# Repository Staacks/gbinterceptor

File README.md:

# GB Interceptor
Capture or stream Game Boy gameplay footage via USB without modifying the Game Boy.

This open source and open hardware Game Boy adapter uses an rp2040 to capture the communication on the cartridge bus. This data is fed into an emulator, rendered and then offered as a USB video class device.

Details about the concept can be found at https://there.oughta.be/a/game-boy-capture-cartridge and an overview is given in the following video:

If you have pull-requests, bug reports or want to contribute new case designs, please do not hesitate to open an issue. For generic discussions, "show and tell" and if you are looking for support for something that is not a problem in the code here, I would recommend .

# Warnings

Please make sure to understand what this device does and what its limitations are. Most importantly, there is a little lag which will make it unsuitable for playing on a bis screen. It might be ok for slow games, but its focus is on recording and streaming.

Also check out the compatibility tables for host software (for example OBS) and particular games. In principle this is a USB video class device and does not require drivers, but not all software supports the unsusual video format of the Interceptor. Similarly, games should usually work, but sometimes there are some details that the Interceptor does not yet support properly and some rare things that cannot work based on the principle of this device.

* [Game Boy compatibility](https://github.com/Staacks/gbinterceptor/wiki/Game-Boy-compatibility)
* [Host software compatibility](https://github.com/Staacks/gbinterceptor/wiki/Host-software-compatibility)
* [Game compatibility](https://github.com/Staacks/gbinterceptor/wiki/Game-compatibility)

# Building the Interceptor

There is an [order and build video](https://youtu.be/Lg92tVkEE98) to guide you through the build process which I highly recommend, especially if you are not used to ordering PCBs. A [written guide can be found in this repository's wiki](https://github.com/Staacks/gbinterceptor/wiki/Build-guide).

# Usage

Simply plug the Interceptor into your Game Boy and the Game into the Interceptor. Connect the Interceptor to your computer before turning on the Game Boy. It should show up as a webcam in any software that supports USB Video devices (for example OBS Studio). Note that some software is not entirely happy with the exotic format, but it should work in most cases (see [Host software compatibility](https://github.com/Staacks/gbinterceptor/wiki/Host-software-compatibility)).

Then just turn on the Game Boy and play.

Note that you do not need to open the video stream first. The only important step is that the Interceptor is powered via USB before the Game Boy is turned on.

## Buttons

The [Mode] button (next to the LEDs) allows to switch between grayscale/green colors and toggle frame blending. Each press switches colors and frame blending is toggled each time it returns to grayscale.

The [Flash] button (near the center, usually inside the case) is only used to flash a new firmware version. Simply hold it while plugging in the USB cable. The Interceptor should appear as a storage device (like a USB stick) and you can simply drag the new firmware file (a uf2 file) into it.

## LEDs

The red LED indicates that the Interceptor is powered.

The blue LED stays on as long as the Interceptor is in sync with the game. (It may shortly turn off for a fraction of a second when the Game Boy turns the display off, i.e. when loading a level.)

# Support

While I do not give any guarantees I (and probably others too) am happy to help if I have the time.

If you are having difficulties to order, build or use your Interceptor, please do not contact me directly but use [r/thereoughtabe on reddit](https://www.reddit.com/r/thereoughtabe/) as this allows others to help and the answer might help others, too.

If you found a bug and in particular if you find glitches in a game, please check the [compatibility lists](https://github.com/Staacks/gbinterceptor/wiki) in the Wiki first to see if it is a known problem and open an issue here on Github otherwise.

# Building the firmware

Most users should just install the latest release uf2 as described in the [Build guide](https://github.com/Staacks/gbinterceptor/wiki/Build-guide), but if you want to build it yourself, you will need the [Raspberry Pi Pico SDK](https://github.com/raspberrypi/pico-sdk). Don't forget to set PICO_SDK_PATH accordingly.

Make sure to check out the submodules too and specifically make sure that the [TinyUSB](https://github.com/hathach/tinyusb) submodule is at least on version 0.14.0 as the Pico SDK currently references an older version. (Also see [#3](https://github.com/Staacks/gbinterceptor/issues/3))

# License
The code is released under the GNU General Public Licence 3 and the design files (PCB layout and 3d printed case) are released under the Creative Commons licence CC-BY 4.0.

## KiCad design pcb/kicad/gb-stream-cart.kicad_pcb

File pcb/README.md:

# GB Interceptor PCB

These are the design files for the PCB of the GB Interceptor. See the [build guide](https://github.com/Staacks/gbinterceptor/wiki/Build-guide) for details.

# License

The design files are licensed under the Creative Commons Attribution License (CC-BY 4.0).

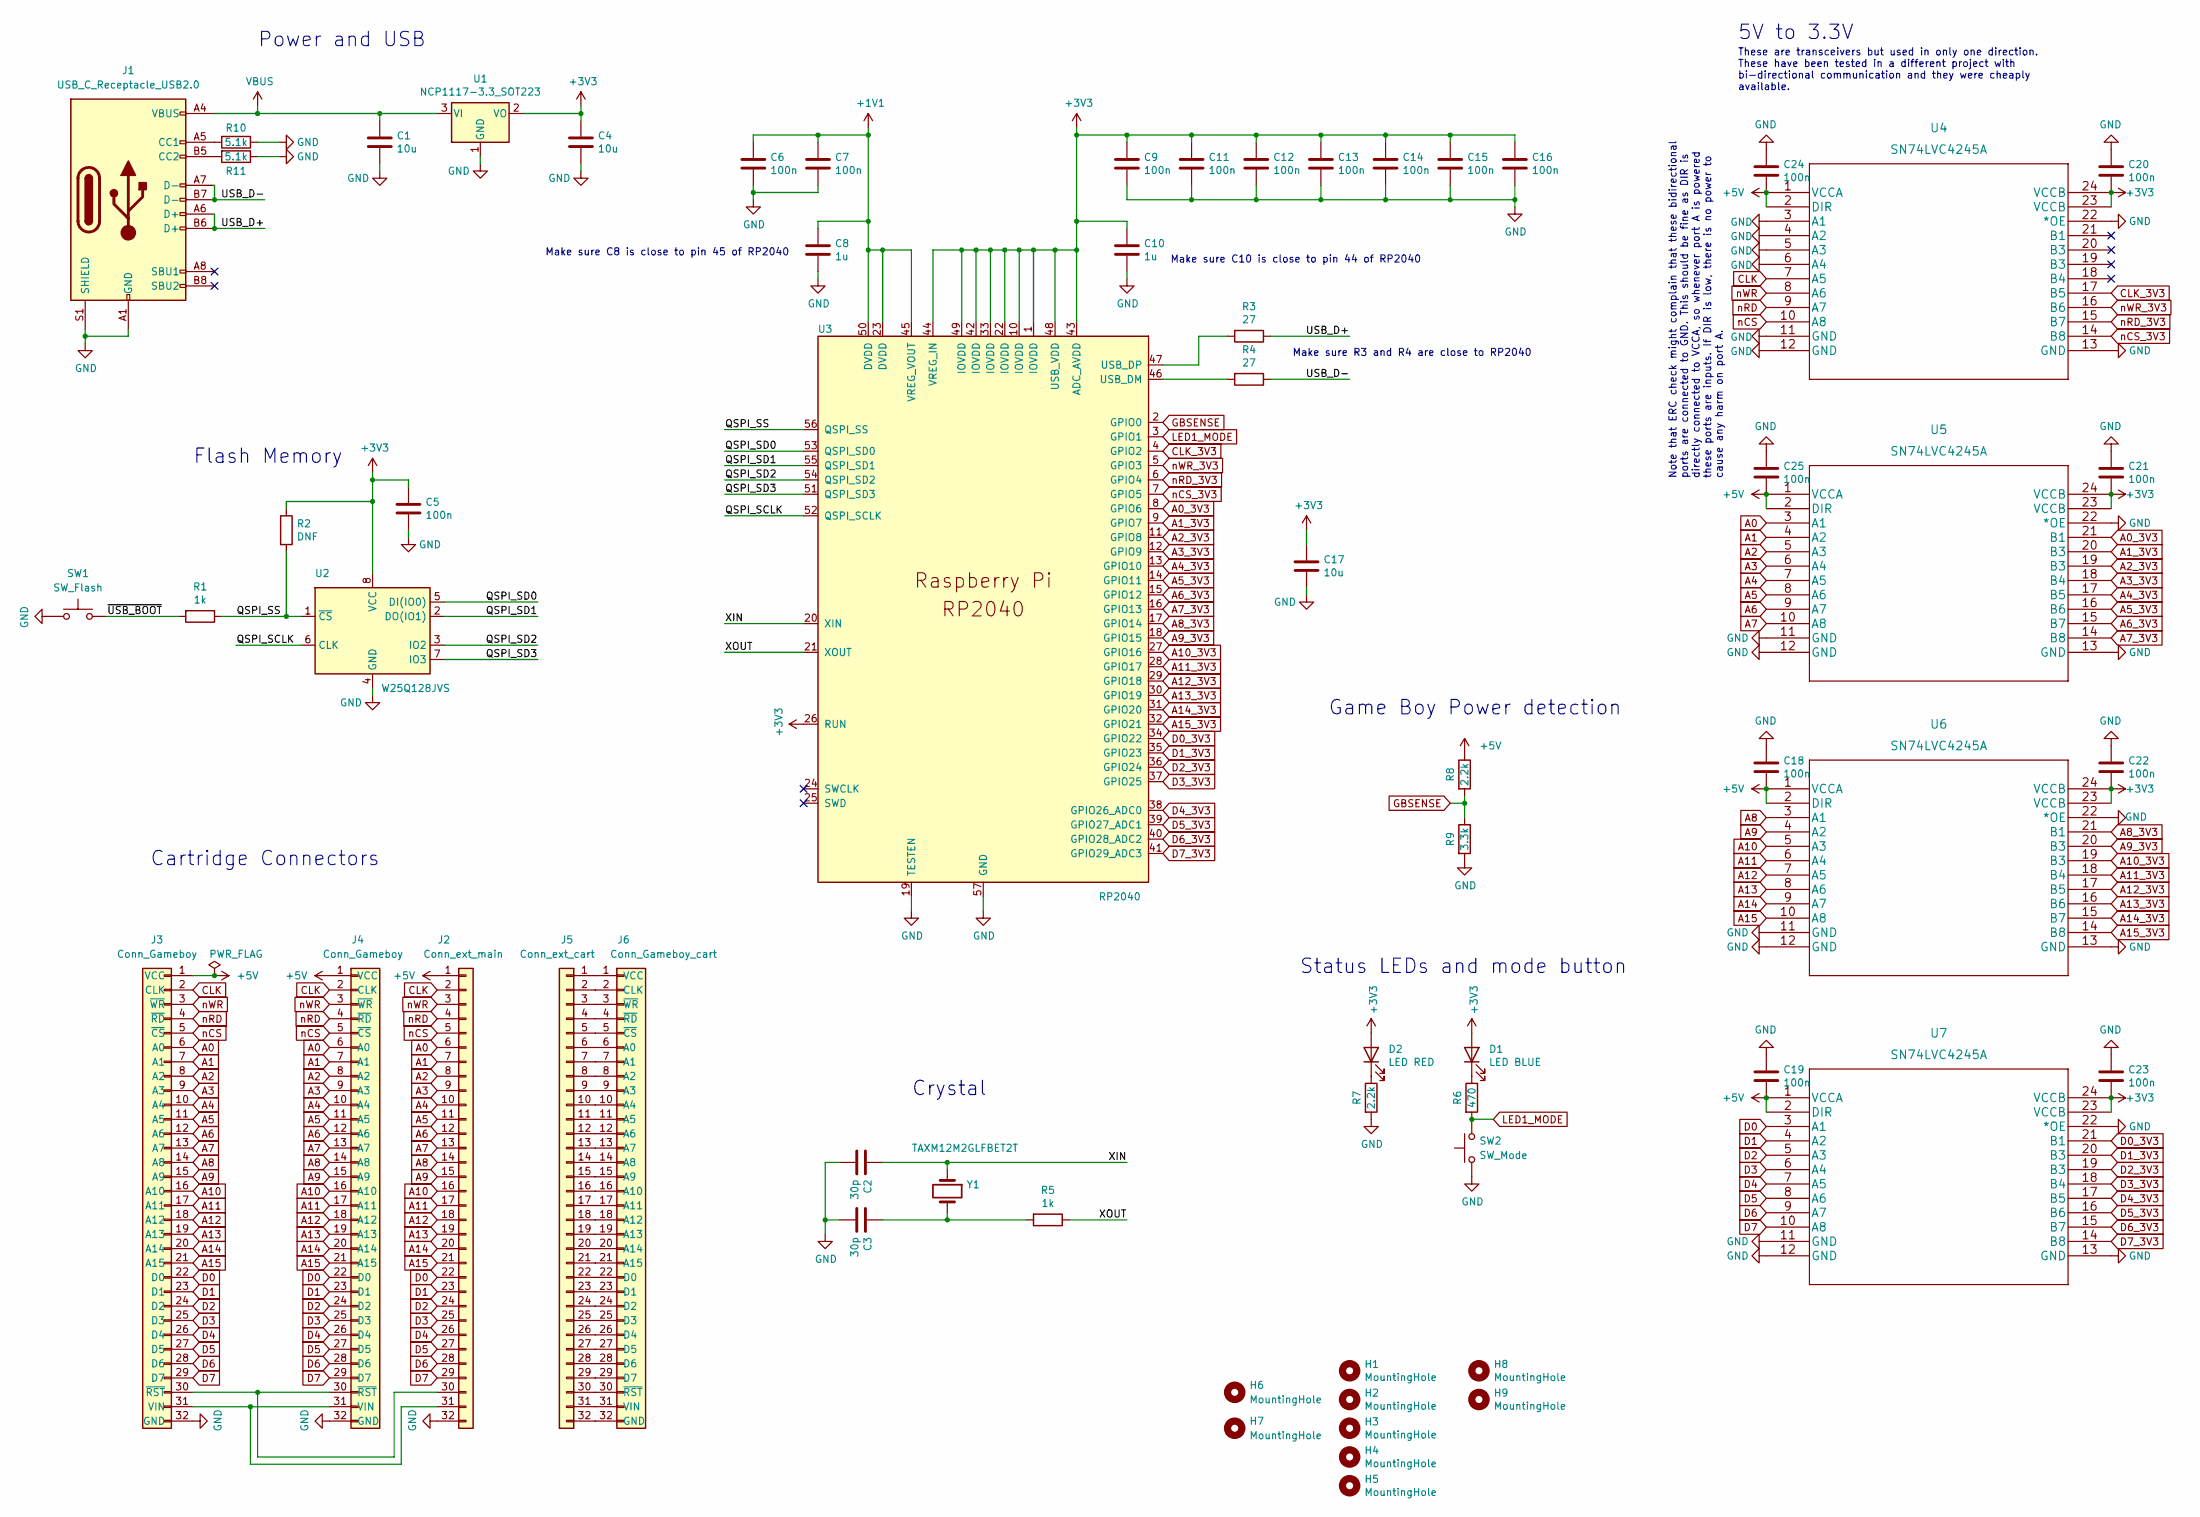
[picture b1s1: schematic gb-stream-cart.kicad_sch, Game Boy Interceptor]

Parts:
C1, C4, C17: 10u; C_0805_2012Metric; LCSC C440198
C2, C3: 30p; C_0402_1005Metric; LCSC C1570
C5, C6, C7, C9, C11, C12, C13, C14, C15, C16, C18, C19, C20, C21, C22, C23, C24, C25: 100n; C_0402_1005Metric; LCSC C1525
C8, C10: 1u; C_0402_1005Metric; LCSC C52923
D1: LED BLUE; LED_1206_3216Metric; LCSC C130717
D2: LED RED; LED_1206_3216Metric; LCSC C84270
H1, H2, H3, H4, H5, H8, H9: MountingHole; MountingHole_2.7mm_M2.5
H6: MountingHole; MountingHole_8.4mm_M8
H7: MountingHole; MountingHole_2.2mm_M2
J1: USB_C_Receptacle_USB2.0; USB_C_Receptacle_HRO_TYPE-C-31-M-12; LCSC C165948
J2: Conn_ext_main; PinHeader_2x16_P2.54mm_Horizontal
J3: Conn_Gameboy; cartridge_PCBedge
J4: Conn_Gameboy; cartridge-slot
J5: Conn_ext_cart; PinHeader_2x16_P2.54mm_Horizontal
J6: Conn_Gameboy_cart; cartridge-slot
R1, R5: 1k; R_0402_1005Metric; LCSC C11702
R2: DNF; R_0402_1005Metric
R3, R4: 27; R_0402_1005Metric; LCSC C25100
R6: 470; R_0402_1005Metric; LCSC C25117
R7, R8: 2.2k; R_0402_1005Metric; LCSC C25879
R9: 3.3k; R_0402_1005Metric; LCSC C25890
R10, R11: 5.1k; R_0402_1005Metric; LCSC C25905
SW1: SW_Flash; SW_Push_1P1T-SH_NO_CK_KMR2xxG; LCSC C72443
SW2: SW_Mode; SW_Push_1P1T-SH_NO_CK_KMR2xxG; LCSC C72443
U1: NCP1117-3.3_SOT223; SOT-223-3_TabPin2; LCSC C146799
U2: W25Q128JVS; SOIC-8_5.23x5.23mm_P1.27mm; LCSC C97521
U3: RP2040; RP2040-QFN-56; LCSC C2040
U4, U5, U6, U7: SN74LVC4245A; SN74LVC4245APWR; LCSC C7859
Y1: TAXM12M2GLFBET2T; Crystal_SMD_HC49-US; LCSC C111117

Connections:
+1V1: C6.1, C7.1, C8.1, U3.23 (DVDD), U3.45 (VREG_VOUT), U3.50 (DVDD)
+3V3: C4.1, C5.1, C9.1, C10.1, C11.1, C12.1, C13.1, C14.1, C15.1, C16.1, C17.1, C20.2, C21.2, C22.2, C23.2, D1.2 (A), D2.2 (A), R2.1, U1.2 (VO), U2.8 (VCC), U3.1 (IOVDD), U3.10 (IOVDD), U3.22 (IOVDD), U3.26 (RUN), U3.33 (IOVDD), U3.42 (IOVDD), U3.43 (ADC_AVDD), U3.44 (VREG_IN), U3.48 (USB_VDD), U3.49 (IOVDD), U4.23 (VCCB), U4.24 (VCCB), U5.23 (VCCB), U5.24 (VCCB), U6.23 (VCCB), U6.24 (VCCB), U7.23 (VCCB), U7.24 (VCCB)
+5V: C18.2, C19.2, C24.2, C25.2, J2.1, J3.1 (VCC), J4.1 (VCC), R8.1, U4.1 (VCCA), U4.2 (DIR), U5.1 (VCCA), U5.2 (DIR), U6.1 (VCCA), U6.2 (DIR), U7.1 (VCCA), U7.2 (DIR)
/QSPI_SCLK: U2.6 (CLK), U3.52 (QSPI_SCLK)
/QSPI_SD0: U2.5 (DI(IO0)), U3.53 (QSPI_SD0)
/QSPI_SD1: U2.2 (DO(IO1)), U3.55 (QSPI_SD1)
/QSPI_SD2: U2.3 (IO2), U3.54 (QSPI_SD2)
/QSPI_SD3: U2.7 (IO3), U3.51 (QSPI_SD3)
/QSPI_SS: R1.1, R2.2, U2.1 (~CS), U3.56 (QSPI_SS)
/USB_D+: J1.A6 (D+), J1.B6 (D+), R3.1
/USB_D-: J1.A7 (D-), J1.B7 (D-), R4.1
/XIN: C2.1, U3.20 (XIN), Y1.1
/XOUT: R5.1, U3.21 (XOUT)
/~USB_BOOT: R1.2, SW1.2
A0: J2.6, J3.6 (A0), J4.6 (A0), U5.3 (A1)
A0_3V3: U3.8 (GPIO6), U5.21 (B1)
A1: J2.7, J3.7 (A1), J4.7 (A1), U5.4 (A2)
A1_3V3: U3.9 (GPIO7), U5.20 (B3)
A2: J2.8, J3.8 (A2), J4.8 (A2), U5.5 (A3)
A2_3V3: U3.11 (GPIO8), U5.19 (B3)
A3: J2.9, J3.9 (A3), J4.9 (A3), U5.6 (A4)
A3_3V3: U3.12 (GPIO9), U5.18 (B4)
A4: J2.10, J3.10 (A4), J4.10 (A4), U5.7 (A5)
A4_3V3: U3.13 (GPIO10), U5.17 (B5)
A5: J2.11, J3.11 (A5), J4.11 (A5), U5.8 (A6)
A5_3V3: U3.14 (GPIO11), U5.16 (B6)
A6: J2.12, J3.12 (A6), J4.12 (A6), U5.9 (A7)
A6_3V3: U3.15 (GPIO12), U5.15 (B7)
A7: J2.13, J3.13 (A7), J4.13 (A7), U5.10 (A8)
A7_3V3: U3.16 (GPIO13), U5.14 (B8)
A8: J2.14, J3.14 (A8), J4.14 (A8), U6.3 (A1)
A8_3V3: U3.17 (GPIO14), U6.21 (B1)
A9: J2.15, J3.15 (A9), J4.15 (A9), U6.4 (A2)
A9_3V3: U3.18 (GPIO15), U6.20 (B3)
A10: J2.16, J3.16 (A10), J4.16 (A10), U6.5 (A3)
A10_3V3: U3.27 (GPIO16), U6.19 (B3)
A11: J2.17, J3.17 (A11), J4.17 (A11), U6.6 (A4)
A11_3V3: U3.28 (GPIO17), U6.18 (B4)
A12: J2.18, J3.18 (A12), J4.18 (A12), U6.7 (A5)
A12_3V3: U3.29 (GPIO18), U6.17 (B5)
A13: J2.19, J3.19 (A13), J4.19 (A13), U6.8 (A6)
A13_3V3: U3.30 (GPIO19), U6.16 (B6)
A14: J2.20, J3.20 (A14), J4.20 (A14), U6.9 (A7)
A14_3V3: U3.31 (GPIO20), U6.15 (B7)
A15: J2.21, J3.21 (A15), J4.21 (A15), U6.10 (A8)
A15_3V3: U3.32 (GPIO21), U6.14 (B8)
CLK: J2.2, J3.2 (CLK), J4.2 (CLK), U4.7 (A5)
CLK_3V3: U3.4 (GPIO2), U4.17 (B5)
D0: J2.22, J3.22 (D0), J4.22 (D0), U7.3 (A1)
D0_3V3: U3.34 (GPIO22), U7.21 (B1)
D1: J2.23, J3.23 (D1), J4.23 (D1), U7.4 (A2)
D1_3V3: U3.35 (GPIO23), U7.20 (B3)
D2: J2.24, J3.24 (D2), J4.24 (D2), U7.5 (A3)
D2_3V3: U3.36 (GPIO24), U7.19 (B3)
D3: J2.25, J3.25 (D3), J4.25 (D3), U7.6 (A4)
D3_3V3: U3.37 (GPIO25), U7.18 (B4)
D4: J2.26, J3.26 (D4), J4.26 (D4), U7.7 (A5)
D4_3V3: U3.38 (GPIO26_ADC0), U7.17 (B5)
D5: J2.27, J3.27 (D5), J4.27 (D5), U7.8 (A6)
D5_3V3: U3.39 (GPIO27_ADC1), U7.16 (B6)
D6: J2.28, J3.28 (D6), J4.28 (D6), U7.9 (A7)
D6_3V3: U3.40 (GPIO28_ADC2), U7.15 (B7)
D7: J2.29, J3.29 (D7), J4.29 (D7), U7.10 (A8)
D7_3V3: U3.41 (GPIO29_ADC3), U7.14 (B8)
GBSENSE: R8.2, R9.1, U3.2 (GPIO0)
GND: C1.2, C2.2, C3.2, C4.2, C5.2, C6.2, C7.2, C8.2, C9.2, C10.2, C11.2, C12.2, C13.2, C14.2, C15.2, C16.2, C17.2, C18.1, C19.1, C20.1, C21.1, C22.1, C23.1, C24.1, C25.1, J1.A1 (GND), J1.A12 (GND), J1.B1 (GND), J1.B12 (GND), J1.S1 (SHIELD), J2.32, J3.32 (GND), J4.32 (GND), R7.2, R9.2, R10.1, R11.1, SW1.1, SW2.1, U1.1 (GND), U2.4 (GND), U3.19 (TESTEN), U3.57 (GND), U4.3 (A1), U4.4 (A2), U4.5 (A3), U4.6 (A4), U4.11 (GND), U4.12 (GND), U4.13 (GND), U4.22 (*OE), U5.11 (GND), U5.12 (GND), U5.13 (GND), U5.22 (*OE), U6.11 (GND), U6.12 (GND), U6.13 (GND), U6.22 (*OE), U7.11 (GND), U7.12 (GND), U7.13 (GND), U7.22 (*OE)
LED1_MODE: R6.2, SW2.2, U3.3 (GPIO1)
unnamed: C3.1, R5.2, Y1.2, Y1.3
unnamed: D1.1 (K), R6.1
unnamed: D2.1 (K), R7.1
unnamed: J1.A5 (CC1), R10.2
unnamed: J1.B5 (CC2), R11.2
unnamed: J2.30, J3.30 (~RST), J4.30 (~RST)
unnamed: J2.31, J3.31 (VIN), J4.31 (VIN)
unnamed: J5.1, J6.1 (VCC)
unnamed: J5.2, J6.2 (CLK)
unnamed: J5.3, J6.3 (~WR)
unnamed: J5.4, J6.4 (~RD)
unnamed: J5.5, J6.5 (~CS)
unnamed: J5.6, J6.6 (A0)
unnamed: J5.7, J6.7 (A1)
unnamed: J5.8, J6.8 (A2)
unnamed: J5.9, J6.9 (A3)
unnamed: J5.10, J6.10 (A4)
unnamed: J5.11, J6.11 (A5)
unnamed: J5.12, J6.12 (A6)
unnamed: J5.13, J6.13 (A7)
unnamed: J5.14, J6.14 (A8)
unnamed: J5.15, J6.15 (A9)
unnamed: J5.16, J6.16 (A10)
unnamed: J5.17, J6.17 (A11)
unnamed: J5.18, J6.18 (A12)
unnamed: J5.19, J6.19 (A13)
unnamed: J5.20, J6.20 (A14)
unnamed: J5.21, J6.21 (A15)
unnamed: J5.22, J6.22 (D0)
unnamed: J5.23, J6.23 (D1)
unnamed: J5.24, J6.24 (D2)
unnamed: J5.25, J6.25 (D3)
unnamed: J5.26, J6.26 (D4)
unnamed: J5.27, J6.27 (D5)
unnamed: J5.28, J6.28 (D6)
unnamed: J5.29, J6.29 (D7)
unnamed: J5.30, J6.30 (~RST)
unnamed: J5.31, J6.31 (VIN)
unnamed: J5.32, J6.32 (GND)
unnamed: R4.2, U3.46 (USB_DM)
unnamed: R3.2, U3.47 (USB_DP)
VBUS: C1.1, J1.A4 (VBUS), J1.A9 (VBUS), J1.B4 (VBUS), J1.B9 (VBUS), U1.3 (VI)
nCS: J2.5, J3.5 (~CS), J4.5 (~CS), U4.10 (A8)
nCS_3V3: U3.7 (GPIO5), U4.14 (B8)
nRD: J2.4, J3.4 (~RD), J4.4 (~RD), U4.9 (A7)
nRD_3V3: U3.6 (GPIO4), U4.15 (B7)
nWR: J2.3, J3.3 (~WR), J4.3 (~WR), U4.8 (A6)
nWR_3V3: U3.5 (GPIO3), U4.16 (B6)

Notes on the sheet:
Status LEDs and mode button
Make sure R3 and R4 are close to RP2040
Note that ERC check might complain that these bidirectional ports are connected to GND. This should be fine as DIR is directly connected to VCCA, so whenever port A is powered these ports are inputs. If DIR is low, there is no power to cause any harm on port A.
Flash Memory
These are transceivers but used in only one direction. These have been tested in a different project with bi-directional communication and they were cheaply available.
Power and USB
Make sure C10 is close to pin 44 of RP2040
Crystal
Make sure C8 is close to pin 45 of RP2040
5V to 3.3V
Cartridge Connectors
Game Boy Power detection

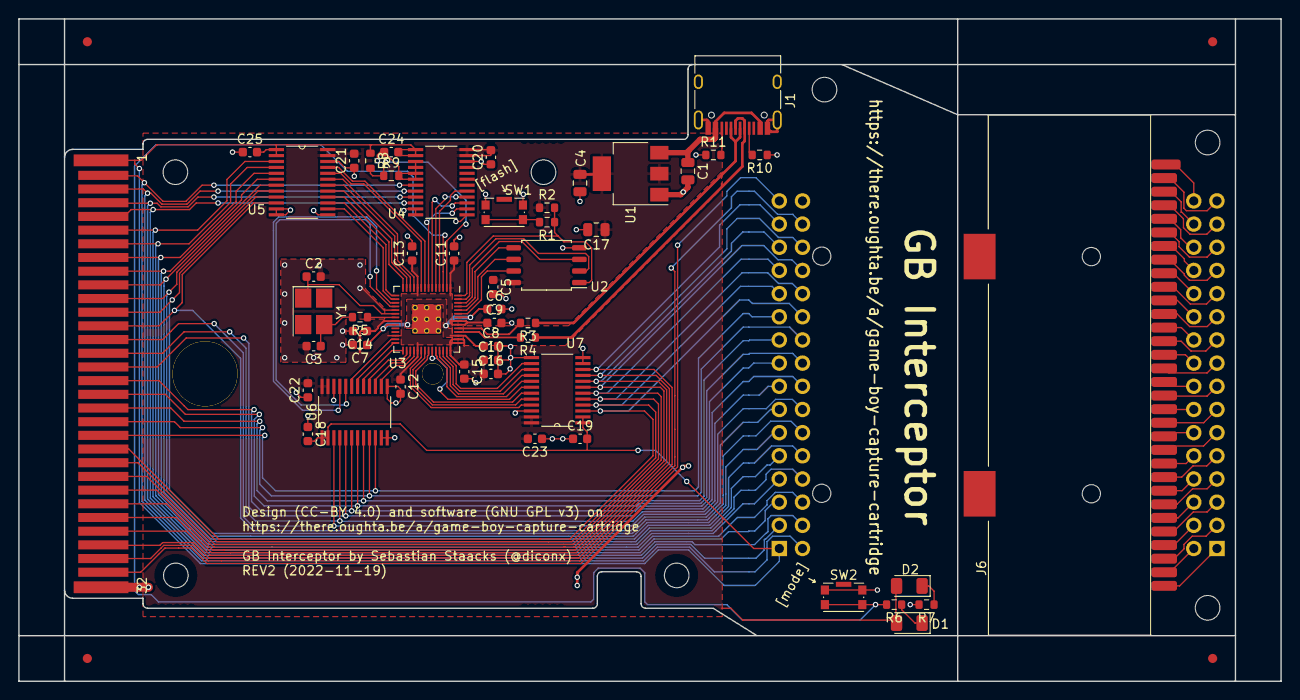
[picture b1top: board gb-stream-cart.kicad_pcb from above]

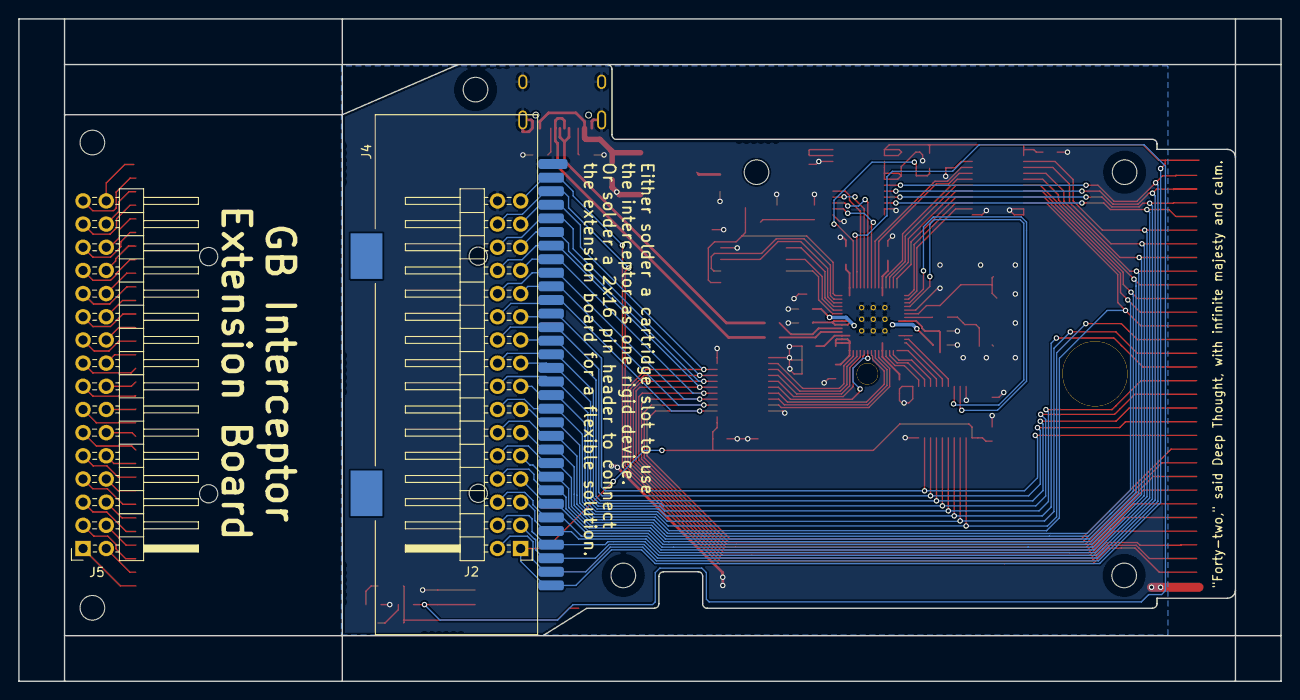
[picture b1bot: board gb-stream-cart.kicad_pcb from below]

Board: 2 copper layers, 138.3 x 72.6 mm, 63 parts (3 on the bottom side), 115 nets.

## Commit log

2022-12-16 Update README.md
    Initial structure for the readme
2022-12-16 Update issue templates
2022-12-16 Initial commit of locally developed project to prepare release.
2022-12-27 Improve USB descriptors: Device name and calculation of bitrate limits.
2022-12-27 Add case variant by AngryHelder.
2022-12-29 Allow setting arbitrary framerates below 29fps, some cleanup and greeting line on terminal.
2022-12-29 Fix flickering on MacOS (Really stupid error forcing new USB frames to be sent during rendering of a line instead of hblank and vblank)
2022-12-29 Add version string and output it when connecting to the Interceptor via its serial endpoint.
2022-12-29 Allow restart without waiting for the Game Boy to be turned off. This should fix #4, but has not yet been tested.
2022-12-29 Add PPU sync for tight loops using the STAT register to wait for vblank.
2022-12-30 Added support for DMA from cartridge. (Not really tested. I thought I found this happening in Donkey Kong III and implemented it. What I did not notice was that the real Game Boy also crashed and tha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
2022-12-30 Fixes for original Game Boy (DMG): Detect return after DMA from SP access to fix Donkey Kong Land. Ignore address on bus when reading from VRAM and use emulated address instead to fix several graphic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
2022-12-30 Fix sync via tight loops if cp [HL] is used.
2022-12-30 Release v1.0.1
2023-01-09 Separate div register from cycleIndex to avoid errors when games reset the div register. Fixing the major problem in #7. (Also refactor emergency stops in opcodes.c)
2023-01-09 Release v1.0.2
2023-01-10 Limit allowed allowed framerate steps to fix issues with apps that freeze otherwise (probably trying to enumerate all options?)
2023-01-10 Only check consistency of stack pointer against addresses on the bus if it is not pointing at VRAM because these adresses are not trustworthy on the DMG (fixes Pokemon red/blue on the DMG)
2023-01-10 Fix: Duplicate detection after immediate return from halt fails if historyIndex points at end of history buffer (Fixing Pokemon yellow).
2023-01-11 Add on screen display to indicate if frame blending is on or off and default to off on start.
2023-01-11 Add tracking of vblank adjustment to PPU timing debug macro
2023-01-11 Show version on standby screen.
2023-01-11 Release v1.0.3
2023-01-14 Fix Interceptor not working after power cycle on some outlier PCBs. Manufacturing tolerances can lead to edge cases in which the olscillator takes to long to settle, which leads to the Interceptor wo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
2023-01-14 Increase lead in time for gathering clock statistics, fixing incorrect clocks an error in many games on the Game Boy Pocket.
2023-01-15 Release v1.0.4
2023-01-20 Add game detection. (Note that most hashes have been generated automatically, but game detection only really becomes relevant for game-specific fixes and time trials, at which point the relevant hash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
2023-01-22 Game-specific fixes for DMA returns and fixin Alien vs. Predator
2023-01-25 Limit register debug script to last 64 events to reduce memory usage.
2023-01-26 Game-specific fixes by reconstructing memory addresses based on conditional jumps and fixing Bonk's Adventure
2023-01-26 Set unique USB serial number based on unique flash ID.
2023-01-27 Option to allow some games to sync to vblank interrupt even if it has been delayed and use that to fix TMNT.
2023-01-27 Fix carry flag for sbc instruction if carry flag was set before operation and result if 0xff or 0xfe. Fixes background-mess of Battletoads (character sprite still broken).
2023-01-28 Replace reconstuct fix function by a non-automated but more efficient and more flexible system of mapping fix operations to the outcome of specific branched. Also introducting a simple fix definition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
2023-01-28 Fix rolling horizontal line in Kirby's Dream Land 2.
2023-01-28 Set a register to zero if this value is obvious from a conditional jump. (Fixing Chase H.Q.)
2023-01-28 Undo previous commit which was just silly (should go to sleep). Instead fix Chase H.Q. by limiting the stat register emulation to mode 1 and 0 as the PPU is not precise enough to distinguish mode 2 a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
2023-01-29 Game-specific setting to copy some HRAM/IO addresses during DMA and use it to fix Tetris 2
2023-01-29 Fix half-carry bit for several opcodes. (Fixing Killer Instinct and possibly others.)
2023-01-30 Allow using conditional branches to sync to specific scanline.
2023-01-30 Fix vblankOffset output in PPU debugging.
2023-01-30 Allow disabling of tight loop sync events. And fix Samurai Shodown with branch based sync.
2023-01-30 Fix rendering of window if it is enabled mid-frame. (Fixes text banners in Samurai Shodown)
2023-01-31 Fix player sprite in Fighting Simulator.
2023-02-03 Add comments to initializations of hardware registers.
2023-02-03 Improve (but not entirely fix) story text of Batman the animated series.
2023-02-04 Fix menu of Mole Mania
2023-02-04 Remove PC jump requirement from interrupt detection to fix Tiny Toons Bab's Big Break. This is a tricky one as this requirement is supposed to prevent an edge case in which a game has a 1 cycle opcod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
2023-02-04 Wait longer for return instruction after DMA before giving up. Fixes Dr. Franken which counts down 0x40*4=256 cycles instead of 40*4=160.
2023-02-04 Add a lower frame blending mode and use this as default. Also change order of modes when pressing the mode button.
2023-02-04 Release v1.1.0
2023-02-05 New sharper monochrome screens
2023-02-10 Further improve window logic: Only pause internal line counter if the window has been disabled midframe. This fixes the credit banners in Prehistoric Man and possibly other games that were broken by 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
2023-02-10 Increase chunks at which frame blending is calculated. This slightly reduces the load on the PPU core at the cost of slightly less responsive USB communication tasks. Seems to be a better compromise 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
2023-02-10 Interrupt sync for stat interrupt with LY=LYC condition. (Fixes rolling line in Prehistorik Man)
2023-02-11 Increase halt timeout for edge cases of halting for an entire frame with slight clock differences (Fixes occasional crash at level start of Prehistorik Man)
2023-06-10 USB Video in bulk transfer mode. This code is currently deactivated as it seems that there is no advantage for this variant. I would guess that the overhead of many 64B transfers on the rp2040 using 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
2023-07-01 MJPEG encoding! Thanks to Ikadzuchi's suggestion (see #17) this enables 60fps and fixes Apple compatibility (issue #1). This commit has a wide impact on several aspects: Idle screens are now 2bit gra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
2023-07-02 Add specific error message for games that try to set GBC double speed mode.
2023-07-02 Fix USB enumeration problems (descriptor mix-up of bulk and isochronous settings, also moved intiial loading of base jpeg to main to do it only once while still handling USB communications in paralle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
2023-07-02 Switch to bulk transfer mode. (Turns out that the mix-up in the defines (see previous commit) means that I have been testing in bulk mode all along and that isochronous mode caused most of the troubl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
2023-07-04 Fix missing EOI because of 32bit copy.
2023-07-04 Add chroma channels to MJPEG to conform to UVC 1.5 and fix compatibility with OBS
2023-07-04 Fix missing EOI again and USB optimizations (in particular disabling CDC as it usually is not required by the user).
2023-07-04 Bring back green mode.
2023-07-06 Fix LYC=LY STAT interrupt detection causing massive negative cycle offset if triggered on LYC=0 with LY on line 153.
2023-07-06 Do not sync on interrupts that occur shortly after writing to the STAT register to avoid the STAT interrupt bug that occurs on DMG and GBP.
2023-07-08 Limit fps choices to 30fps and 60fps. If 60fps is selected, no chroma channel is used in-game. If 30fps is selected, the higher compatibility with chroma is used and only every second frame is transf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
2023-08-05 Limit framerate of standby screen to 30fps if in 30fps mode and make this release 1.2.0.
2024-01-06 KiCad version update
2024-01-07 Replace various components to improve ease of hand assembly
2024-01-07 Replace mouse bites with V-score to improve depaneling results
2024-01-07 Bump fiducials
2024-01-14 Create dummy CI workflow
2024-01-14 Try to build firmware in CI pipeline using CMake + ninja
2024-01-14 Update main.yml: install arm-none-eabi-gcc toolchain
2024-01-14 Update main.yml: try to install toolchain once again
2024-01-14 Update main.yml: upload build artifacts
2024-01-14 Update main.yml: pin pico-sdk to a specific commit
2024-01-14 Update main.yml: pin version of pico-sdk... not gbinterceptor
2024-01-15 Update main.c: tinyusb bsp/board-related include files
2024-09-07 Update Pico SDK to 2.0.0 for automatic builds. Local testing seems to not require any changes, so let's see if automatic builds are still working properly after such a long time...
2024-09-07 Allow building a base video mode version by setting the precompiler define BASE_VIDEO_MODE. This mode only accepts 30fps and does not allow enabling frame blending or green mode. This is not relevant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
2024-09-07 Automatically build normal and base video mode variant of firmware
2024-09-07 Fix automatic build of base video mode executes rm in wrong directory
2024-09-07 Fixing error of rm in automatic build
2024-09-07 Still trying to automatically build the base video mode variant
2024-09-07 There is a reason I am doing this in a seperate branch...
2024-09-08 Auto-build default and base vide mode variant (#30)

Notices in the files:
pcb/kicad/gb-stream-cart.kicad_pcb:
Licence: Creative Commons Attribution 4.0 International (CC-BY 4.0)
Design (CC-BY 4.0) and software (GNU GPL v3) on
